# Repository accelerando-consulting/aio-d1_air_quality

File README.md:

# Accelerando IoT - Air Quality shield for D1 Bus

This shield is designed to take one of two kinds of dust sensor

* **Sharp GP2Y10** inexpensive LED sensor (cheap but rather low accuracy) [datasheet](https://www.sparkfun.com/datasheets/Sensors/gp2y1010au_e.pdf) [buy](https://s.click.aliexpress.com/e/_DnckA8B)

* **Nova Fitness SDS011** laser sensor [info](https://www.hackster.io/taunoerik/using-sds011-dust-sensor-01f019) [more info](https://aqicn.org/sensor/sds011/) [buy](https://s.click.aliexpress.com/e/_DFAZipD)

The shield also has I2C headers (note, using the Lolin VCDG pinout not the nowadays quasi standard QWIIC GVDC pinout!) which allow attaching a variety of temperature, humidity and other sensors (eg you might like volatile organic compounds, or CO2).

# Suggested sensors

The semi-ubitquitous DHT12 or AM2302 temp/humidity sensors are cheap and cheerful. [buy](https://s.click.aliexpress.com/e/_DDiA6Bz)

The BMP180 temperature/pressure sensor likewise. [buy](https://s.click.aliexpress.com/e/_Dd1bUF5)

In the COVID era CO2 is of interest, you may like the [MH-Z19](https://s.click.aliexpress.com/e/_DBv9ynl) sensor for this.   The Sensirion sensor is the gold standard but runs about $100.  

# Software

If you're using Arduino, just search for the names of your sensors in the library manager.

If you want a leg up, check out our [Stacx](https://github.com/accelerando-consulting/stacx) framework which provides a ready-to-use MQTT sensor runtime for ESP8266 and ESP32 (It's Arduino-based, too).

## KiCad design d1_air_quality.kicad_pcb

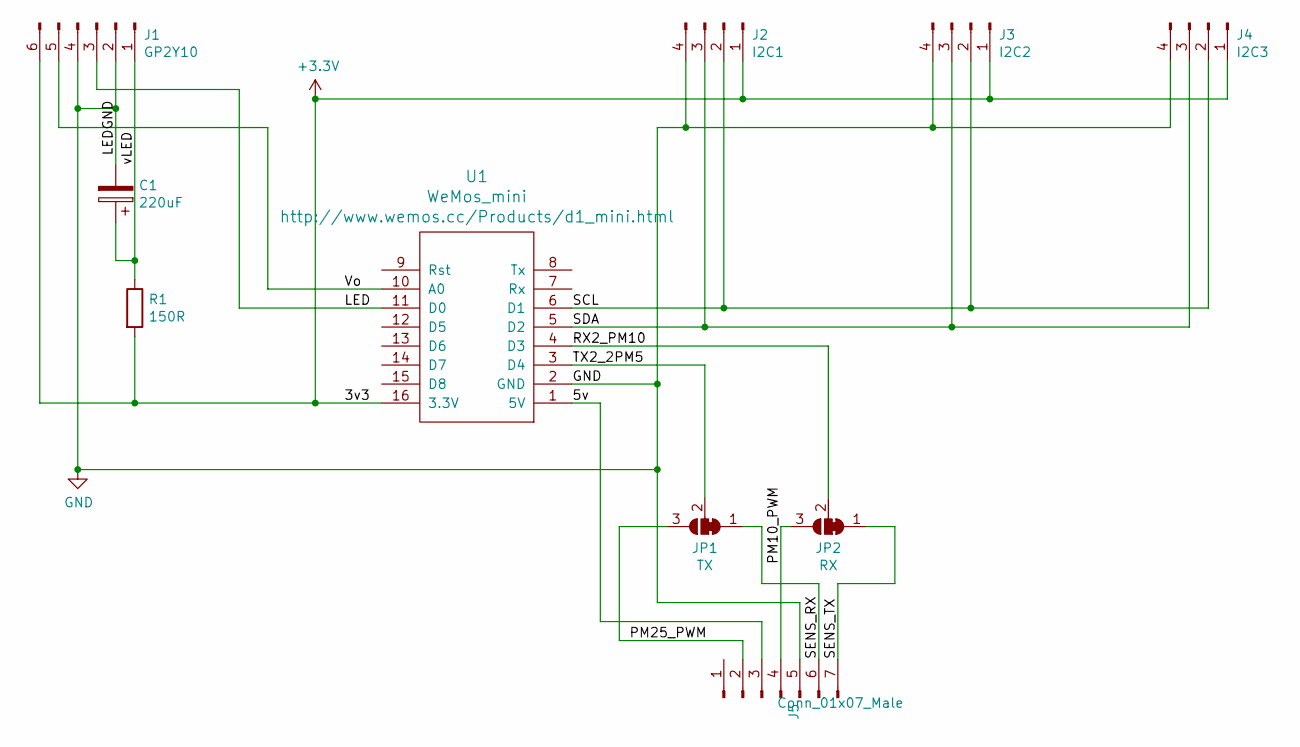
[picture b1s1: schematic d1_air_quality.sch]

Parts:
C1: 220uF; CP_Elec_6.3x7.7
J1: GP2Y10; JST_ZE_BM06B-ZESS-TBT_1x06-1MP_P1.50mm_Vertical
J2: I2C1; JST_SH_SM04B-SRSS-TB_1x04-1MP_P1.00mm_Horizontal
J3: I2C2; JST_SH_SM04B-SRSS-TB_1x04-1MP_P1.00mm_Horizontal
J4: I2C3; JST_SH_SM04B-SRSS-TB_1x04-1MP_P1.00mm_Horizontal
J5: Conn_01x07_Male; JST_XH_B7B-XH-AM_1x07_P2.50mm_Vertical
JP1: TX; SolderJumper-3_P1.3mm_Bridged12_Pad1.0x1.5mm
JP2: RX; SolderJumper-3_P1.3mm_Bridged12_Pad1.0x1.5mm
R1: 150R; R_0603_1608Metric
U1: WeMos_mini; wemos-d1-mini-with-pin-header

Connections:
+3V3: J1.6, J2.1, J3.1, J4.1, R1.2, U1.16 (3.3V)
/5v: J5.3, U1.1 (5V)
/LED: J1.3, U1.11 (D0)
/PM10_PWM: J5.4, JP2.3 (B)
/PM25_PWM: J5.2, JP1.3 (B)
/RX2_PM10: JP2.2 (C), U1.4 (D3)
/SCL: J2.2, J3.2, J4.2, U1.6 (D1)
/SDA: J2.3, J3.3, J4.3, U1.5 (D2)
/SENS_RX: J5.6, JP1.1 (A)
/SENS_TX: J5.7, JP2.1 (A)
/TX2_2PM5: JP1.2 (C), U1.3 (D4)
/Vo: J1.5, U1.10 (A0)
/vLED: C1.1, J1.1, R1.1
GND: C1.2, J1.2, J1.4, J2.4, J3.4, J4.4, J5.5, U1.2 (GND)

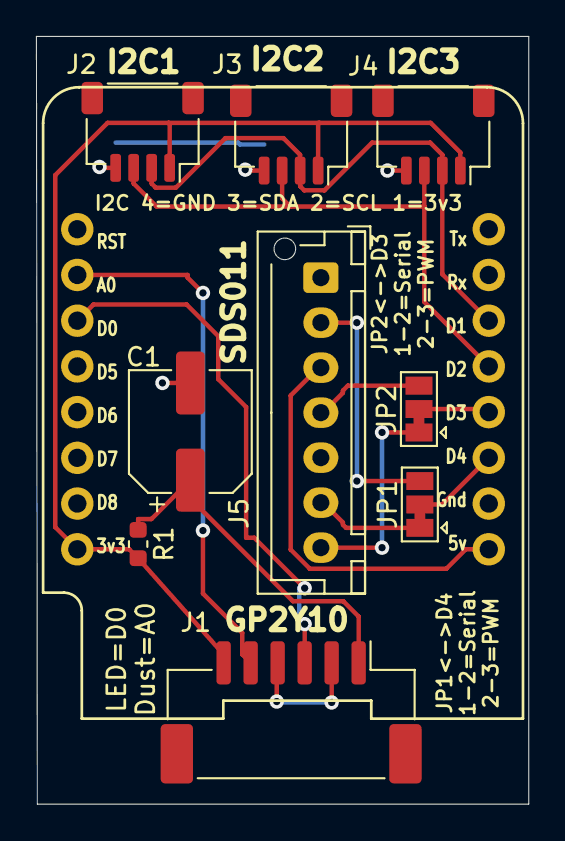
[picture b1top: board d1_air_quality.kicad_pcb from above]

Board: 2 copper layers, 27.4 x 42.7 mm, 10 parts (0 on the bottom side), 14 nets.

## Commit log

2019-09-14 D1 shields for various client projects
2022-04-12 D1 air quality module v1
2022-11-09 Add basic doco
2022-11-09 pictures
2022-11-09 Add links for sensors
